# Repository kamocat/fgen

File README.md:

# fgen
A simple amplifier for a phone-based function generator

You'll need to install an app on your phone to actually generate the signal.
I recommend this one: https://play.google.com/store/apps/details?id=com.keuwl.functiongenerator

## Update:
It turns out the function generator does a pretty poor job of generating square waves above 1kHz, and the triangle waves are marginably passable. This could be a problem with the phone or the slew rate of the op-amp. I didn't have any capacitors larger than 100uF, so it can really only put out 50mA at full voltage. To top it off, the the function generator output depends on the phone's volume settings, and the offset feature doesn't work (probably due to a decoupling capacitor in the phone). Maybe I should switch to an MQTT-controlled ESP32.

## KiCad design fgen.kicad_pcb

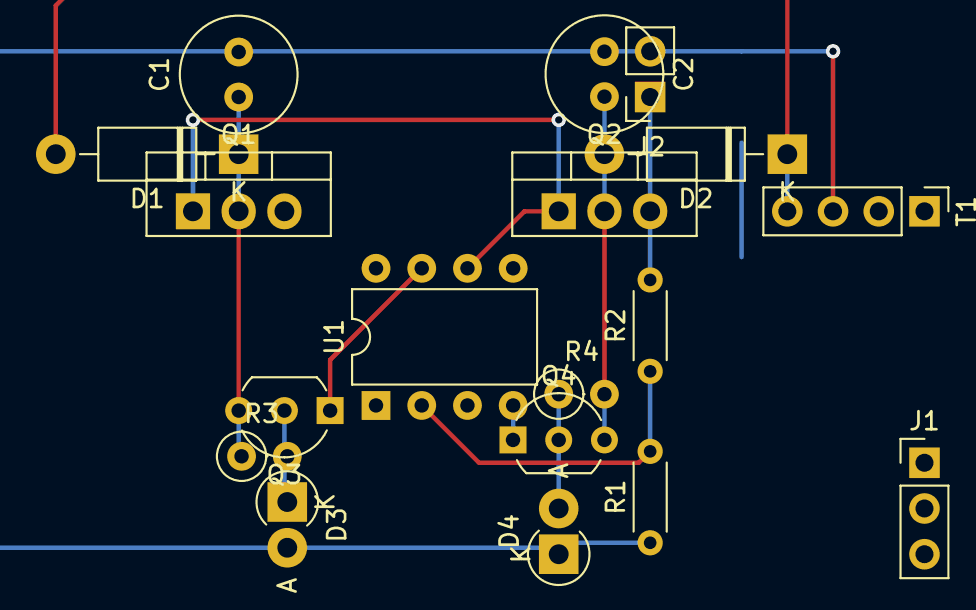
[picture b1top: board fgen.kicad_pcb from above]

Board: 2 copper layers, 18 parts (0 on the bottom side), 12 nets.

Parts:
C1, C2: 680uF; C_Radial_D6.3mm_H5.0mm_P2.50mm
D1, D2: 1N4004; D_DO-41_SOD81_P10.16mm_Horizontal
D3, D4: 15V; D_DO-41_SOD81_P2.54mm_Vertical_AnodeUp
J1: AudioPlug3; PinHeader_1x03_P2.54mm_Vertical
J2: Conn_01x02_Female; PinSocket_1x02_P2.54mm_Vertical
Q1: TIP29C; TO-220-3_Vertical
Q2: TIP30C; TO-220-3_Vertical
Q3: 2N3904; TO-92_Inline_Wide
Q4: 2N3906; TO-92_Inline_Wide
R1: 470; R_Axial_DIN0204_L3.6mm_D1.6mm_P5.08mm_Horizontal
R2: 100k; R_Axial_DIN0204_L3.6mm_D1.6mm_P5.08mm_Horizontal
R3, R4: 10k; R_Axial_DIN0207_L6.3mm_D2.5mm_P2.54mm_Vertical
T1: Transformer_1P_1S; PinHeader_1x04_P2.54mm_Vertical
U1: LM741; DIP-8_W7.62mm

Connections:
+15V: Q3.1 (E), U1.7 (V+)
+VDC: C1.1, D1.1 (K), Q1.2 (C), Q3.3 (C), R3.1
-15V: Q4.1 (E), U1.4 (V-)
-VDC: C2.2, D2.2 (A), Q2.2 (C), Q4.3 (C), R4.2
/Vout: J2.1, Q1.3 (E), Q2.3 (E), R2.2
/ctrl: Q1.1 (B), Q2.1 (B), U1.6
/fb: R1.2, R2.1, U1.2 (-)
/left: J1.1 (T), U1.3 (+)
GND: C1.2, C2.1, D3.2 (A), D4.1 (K), J1.2 (S), J2.2, R1.1, T1.3 (SA)
unnamed: D1.2 (A), D2.1 (K), T1.4 (SB)
unnamed: D3.1 (K), Q3.2 (B), R3.2
unnamed: D4.2 (A), Q4.2 (B), R4.1

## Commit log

2022-03-29 first draft in progress
2022-03-29 first draft
2022-03-29 Breadboard layout done
2022-03-30 schematic bug fix
2022-03-30 Prototyped on breadboard, updated gain resistor
